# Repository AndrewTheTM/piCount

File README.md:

# Raspberry Pi Truck Counting System

This is a system to eventually count trucks using a Raspberry Pi and it's camera.
Ideally, this would be placed near a business (with a known number of employees).
Currently, there is a classifier included for cars based on the instructions at
http://abhishek4273.com/2014/03/16/traincascade-and-car-detection-using-opencv/.

# The Plan

I've collected some internet pictures of trucks that I am going to use to train
the classifier for trucks.  I will also set this up to save images and count the
frames to see what the count is and do some comparisons (eventually).

One of the biggest (if not _THE_ biggest) todo items is to make this run even
when someone isn't pulling up the webpage.  That sounds more difficult than it
likely will be.

# Included

The included classifier (cascade.xml) is for cars and trucks.  I generated it
using the instructions on the link above.  

piCount.py is the actual program.  It runs a python service that can be
viewed by going to http://ip_address:9090.  This runs extremely slow as it is,
so I would highly recommend not using it as a streaming server.

Don't use piTruckTrain.py yet.  I haven't been working on it.

# Current Status

Don't use this yet.  Please.  If you want to help, contact Andrew Rohne @okiAndrew or arohne@oki.org

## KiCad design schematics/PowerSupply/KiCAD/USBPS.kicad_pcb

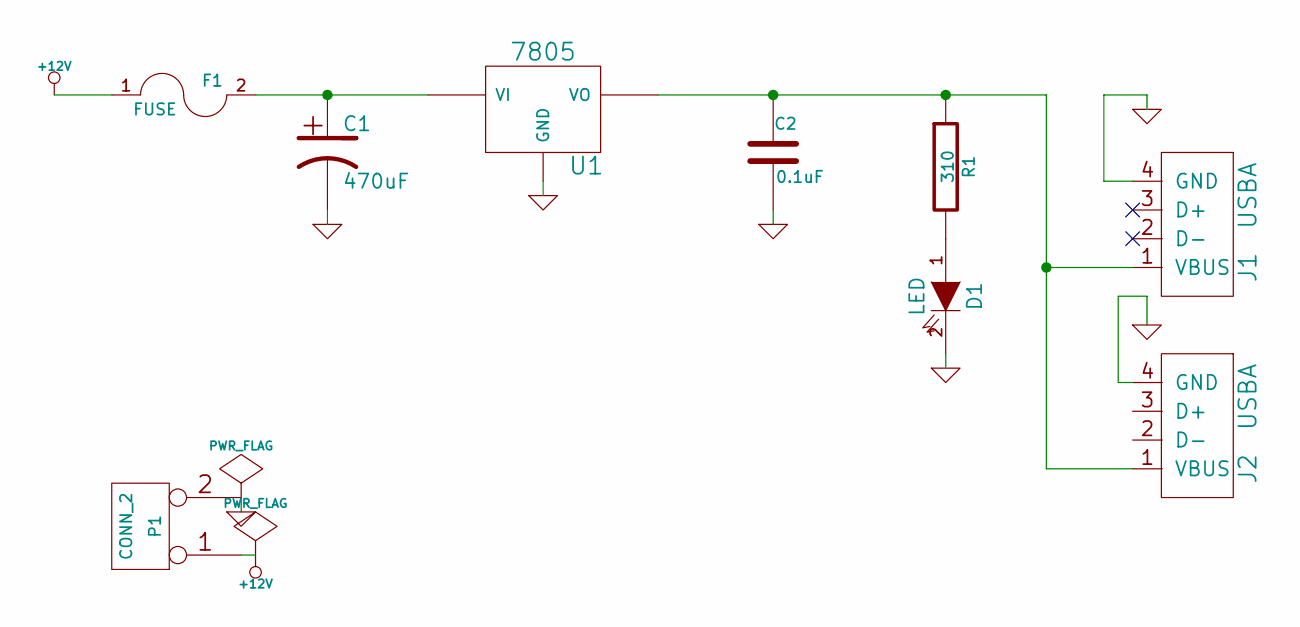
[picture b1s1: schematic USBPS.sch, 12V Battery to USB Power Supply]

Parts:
C1: 470uF
C2: 0.1uF; 0805
D1: LED
F1: FUSE
J1, J2: USBA
P1: CONN_2
R1: 310
U1: 7805

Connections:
+12V: F1.1, P1.1
GND: C1.2, C2.2, D1.2 (K), J1.4 (GND), J1.5, J1.6, J2.4 (GND), J2.5, J2.6, P1.2 (PM), U1.2 (GND)
unnamed: D1.1 (A), R1.2
unnamed: C2.1, J1.1 (VBUS), J2.1 (VBUS), R1.1, U1.3 (VO)
unnamed: C1.1, F1.2, U1.1 (VI)

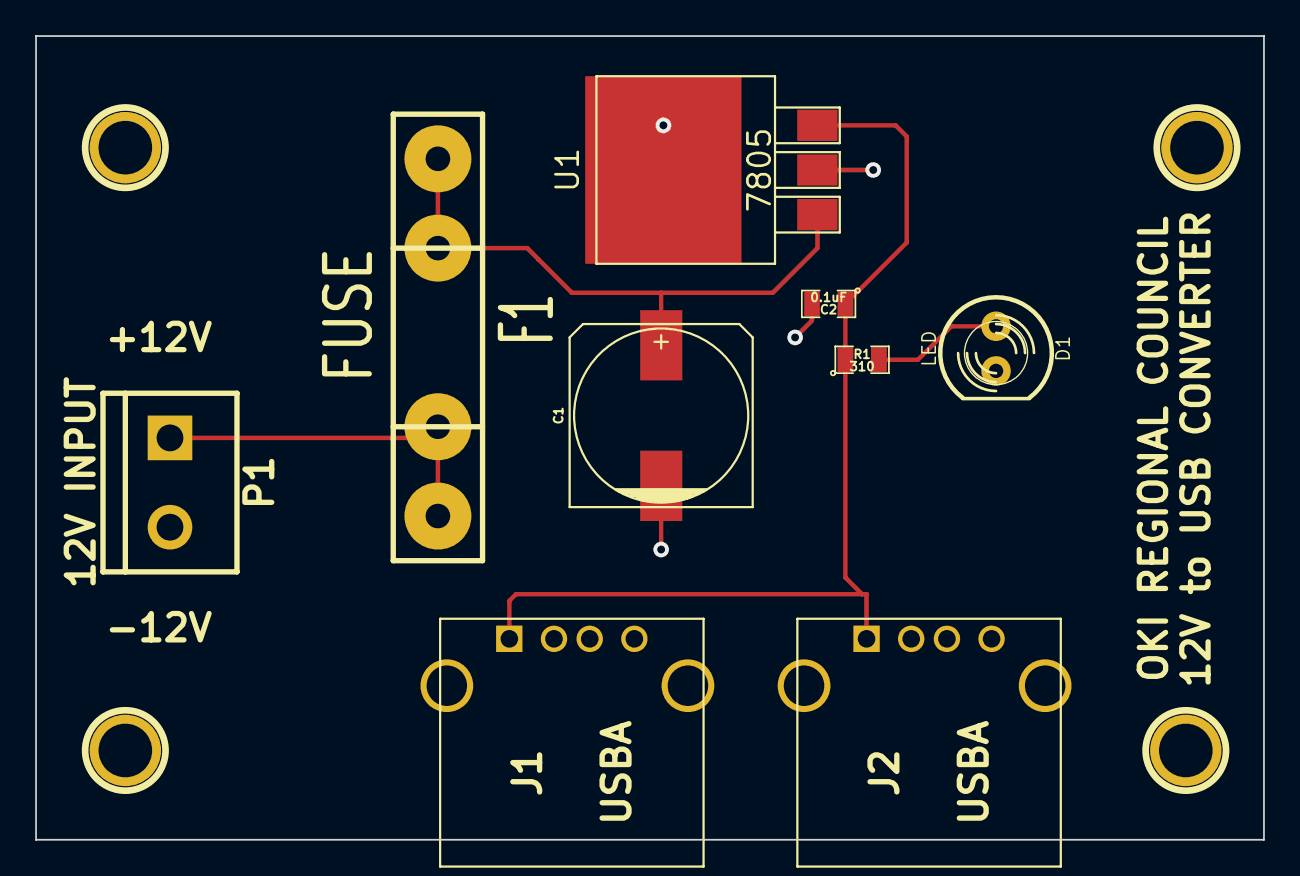
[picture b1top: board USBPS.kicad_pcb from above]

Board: 2 copper layers, 69.8 x 45.7 mm, 9 parts (0 on the bottom side), 5 nets.

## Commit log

2015-08-26 added vehicle images (soon to be removed)
2015-08-26 added batch
    Because copy/paste over a VPN sucks
2015-08-27 Making it for pi
2015-08-27 more pi
2015-08-27 Added readme file
2015-08-27 minor issue
2015-08-27 monkeying around with camera
2015-08-27 image conversion not working
2015-08-27 image issues... checking
2015-08-27 image issues
2015-08-27 fixing camera conflict
2015-08-27 FUCK YOUR FUCKING INDENTS PYTHON
2015-08-27 oops. Missed a global
2015-08-27 changed delay
2015-08-27 blech
2015-08-27 changed to run-once
2015-08-27 minor fixes'
2015-08-27 actually seeing images
2015-08-27 trying for images
2015-08-28 moved around variables, trying to get image to update
2015-08-28 images update, cleaning up code
2015-08-28 face detection
2015-08-28 oops
2015-08-28 code cleanup, bugfix
2015-08-28 adding back detection
2015-08-28 debugging
2015-08-28 issues loading classifier xml
2015-08-28 minor change to show color
2015-08-28 Cleanup
2015-08-28 readme update
2015-08-28 Code cleanup, moved loading classifier file out of loop
2015-08-28 added a util to find the path (I keep getting NOTHING)
2015-08-28 trying without picamera
2015-08-28 turning back for Rpi
2015-08-28 tuning
2015-09-02 added switch to turn on/off image recognition
2015-09-02 don't use this commit
2015-09-02 turned image save off and recog back on
2015-09-03 adding helper for positives
2016-05-18 added new motion detector
2016-05-19 Updated motioncap3 for Raspberry Pi
2016-05-19 Added threading to picamera
2016-05-19 Pulled threading lib out to own file
2016-05-19 typo
2016-05-19 On-pi changes
2016-05-19 added 2 second wait to see if the pi will start to work
2016-05-19 some error trapping
2016-05-19 more error trapping, trying to not have camera conflict
2016-05-19 maybe reordering will fix things
2016-05-19 it works. Trying to add in a better bg subtractor
2016-05-19 Trying to add in a better bg subtractor
2016-05-23 it works. Using better bg subtractor
2016-05-23 it works. Trying a few things with the mask.
2016-05-23 d'oh!
2016-05-23 error in kernel
2016-05-23 better error handling?
2016-05-23 increased kernel matrix to 10x10
2016-05-23 trying to place images side-by-side
2016-05-23 undo last
2016-05-23 fine tuning kernels
2016-05-23 changed background subtractor
2016-05-23 fine tuning kernels and masking algs
2016-05-24 contours
2016-05-24 forget contours, going to keypoints)
2016-05-24 can I mask this?
2016-05-24 detect keypoints only on mask?
2016-05-24 kernel adjustment
2016-05-24 blob detector adjustments
2016-05-25 mask adjustment
2016-05-25 revert mask
2016-05-26 Added beginnings of an Arduino Shield Schematic for power checking
2016-06-07 Power supply PCB finished
2016-06-07 Finished power supply schematic and PCB
